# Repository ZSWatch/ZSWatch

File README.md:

# [zswatch.dev](https://zswatch.dev/)

<div align="center">

<sub>
  ZSWatch v4 CNC:ed Stainless Steel (left), Clear Resin 3D print (right)
</sub>
</div>

> **WatchDK** - The ZSWatch development kit ($99) has the same nRF5340 chip and sensors as the final watch, in a larger form factor for development and debugging. Battery optional, runs off USB-C.
>
> [Order from Elecrow](https://www.elecrow.com/zswatch-development-kit.html)
>
> [Quick Start](https://zswatch.dev/docs/getting-started/watchdk-quickstart)

## About

Smartwatch built from scratch, both hardware and software. Built on the [Zephyr™ Project](https://www.zephyrproject.org/) RTOS, hence the name **ZSWatch** (*Zephyr Smartwatch*).

<kbd></kbd>

<sub>ZSWatch Development Kit (WatchDK)</sub>

https://github.com/ZSWatch/ZSWatch/assets/4318648/ec1a94fd-a682-4559-9e68-f3e5bfcbe682

## Documentation

Full documentation is available at **[zswatch.dev](https://zswatch.dev)**:

- [Getting Started](https://zswatch.dev/docs/getting-started/watchdk-quickstart) - WatchDK quick start guide
- [Toolchain & Compiling](https://zswatch.dev/docs/development/toolchain) - Environment setup, building, and flashing
- [Writing Apps](https://zswatch.dev/docs/development/writing_apps) - How to create applications for ZSWatch
- [Hardware Design](https://zswatch.dev/docs/hardware-design) - PCB design documentation

## Features

### Hardware

- nRF5340 BLE chip ([u-blox NORA-B10 module](https://www.u-blox.com/en/product/nora-b1-series-open-cpu))
  - 128 MHz Dual core
  - 512 KB RAM
  - 1 MB Flash
  - 30 MHz SPI for display
- [240x240 round display](https://www.buydisplay.com/catalog/product/view/id/1849/s/240x240-round-ips-tft-lcd-display-1-28-capacitive-touch-circle-screen/) with touch screen
- IMU [Bosch BMI270](https://www.bosch-sensortec.com/media/boschsensortec/downloads/datasheets/bst-bmi270-ds000.pdf) for gesture navigation, wrist-wake, step counting
- Bosch [BMP581](https://www.bosch-sensortec.com/products/environmental-sensors/pressure-sensors/bmp581/) High-performance pressure sensor (~20 cm accuracy)
- ST [LIS2MDLTR](https://www.st.com/resource/en/datasheet/lis2mdl.pdf) Magnetometer
- Macronix [MX25U51245GZ4I00](https://www.mouser.de/datasheet/2/819/MX25U51245G_2c_1_8V_2c_512Mb_2c_v1_4-3371129.pdf) 64 MB external flash
- Broadcom [APDS-9306-065](https://docs.broadcom.com/docs/AV02-4755EN) Light Sensor for automatic brightness control
- Micro Crystal [RV-8263-C8](https://www.microcrystal.com/en/products/real-time-clock-rtc-modules/rv-8263-c8) RTC for time keeping and alarm functions
- Knowles [SPK0641HT4H-1](https://www.knowles.com/docs/default-source/model-downloads/spk0641ht4h-1-rev-a.pdf) I2S microphone for audio recording
- Nordic [nPM1300](https://docs.nordicsemi.com/category/npm1300-category) PMIC for power and system management
- Speaker (Requires HR Extension Board)

#### PCB

All hardware is designed in KiCad. Hardware repos:

- [Watch PCB](https://github.com/ZSWatch/Watch-HW) - 38 mm diameter watch PCB
- [Watch DevKit PCB](https://github.com/ZSWatch/Watch-DevKit-HW) - Larger development board with breakout headers and debug header
- [Extension PCB](https://github.com/ZSWatch/Extension-HW) - Health and audio addon PCB
- [Dock/Breakout PCB](https://github.com/ZSWatch/Dock-HW) - USB-C breakout for debugger and UART access

<kbd></kbd>
#### HR Extension Board (WIP)

The Extension PCB is a small add-on board (approximately 16.8 mm diameter) that plugs into the WatchDK headers. It is still in development and the design, BOM, and firmware support may change.

More background and progress updates:
- https://zswatch.dev/blog/dk-and-hr-integration
- https://zswatch.dev/blog/progress-hw-xip-usb-power
- https://zswatch.dev/blog/progress-hr-fota

Key BOM highlights:
- Analog Devices / Maxim `MAX86141` optical AFE + ams OSRAM `SFH 7016` (RGB/IR LED module) + Vishay `VEMD8082` photodiodes
- Analog Devices / Maxim `MAX32664` biometric sensor hub
- Renesas / Dialog `DA7212` audio codec (speaker support)
- Amphenol `101P014FB110` board-to-board connectors

### Software

- Bluetooth LE communications via the [ZSWatch Companion App](https://zswatch.dev/docs/getting-started/companion_app) (iOS/Android) or [GadgetBridge](https://codeberg.org/Freeyourgadget/Gadgetbridge) (Android)
- Multiple watchfaces (dynamically switchable), showing time, date, battery, weather, steps, notifications, environmental data, and more
- Pop-up notifications
- Application picker with extensible app framework
  - [Settings](app/src/applications/settings/), [Music control](app/src/applications/music_control/), [Compass](app/src/applications/compass/), and many more
- Step counting, gestures, and much more

The watch also supports ESP32 watchfaces from [Felix Biego](https://github.com/fbiego). See [this fork](https://github.com/Kampi/esp32-lvgl-watchface) for details.

### Smartphone Communication

**iOS (recommended):** Use the official [ZSWatch Companion App](https://apps.apple.com/us/app/zswatch/id6759058602) on the App Store. ZSWatch also supports native [Apple Notification Center Service](https://developer.apple.com/library/archive/documentation/CoreBluetooth/Reference/AppleNotificationCenterServiceSpecification/Specification/Specification.html) and [Apple Media Service](https://developer.apple.com/library/archive/documentation/CoreBluetooth/Reference/AppleMediaService_Reference/Specification/Specification.html).

**Android (experimental companion app):** The ZSWatch Companion App currently requires invite access. Request access via [Discord](https://discord.gg/8XfNBmDfbY) or email [mail@zswatch.dev](mailto:mail@zswatch.dev). For a stable experience, use [GadgetBridge](https://codeberg.org/Freeyourgadget/Gadgetbridge).

See [phone setup on zswatch.dev](https://zswatch.dev/docs/getting-started/phone_setup) for details.

### Enclosure/Casing

3D-printed casing with 3D-printed buttons, with an option for CNC:ed metal casing.

## Getting a WatchDK or Building Your Own

**For development:** The [WatchDK](https://zswatch.dev/docs/getting-started/watchdk-quickstart) ($99) is the recommended starting point. It has the same nRF5340 SoC, sensors, and display as the final watch, with breakout headers, USB-C with SWD/UART, power measurement headers, and a debug header. Everything except battery is included. Battery is optional.

Order WatchDK from Elecrow: [www.elecrow.com/zswatch-development-kit.html](https://www.elecrow.com/zswatch-development-kit.html)

**For DIY builders:** Head over to the hardware repos for the for ordering information. The final miniature watch hardware is still being developed.

## Demos

- [HTTP requests over BLE through Gadgetbridge](https://github.com/ZSWatch/ZSWatch/assets/4318648/12d6e754-ceb3-4efd-9a75-d207aaeb0e82)
- [Watchfaces](https://github.com/ZSWatch/ZSWatch/assets/4318648/13e43401-1c00-40ab-866f-e6518e61940d)

## Developing

See the [Toolchain & Build Guide](https://zswatch.dev/docs/development/toolchain) for environment setup, compiling, and flashing.

To learn how to write apps for ZSWatch, see [Writing Apps](https://zswatch.dev/docs/development/writing_apps).

## Licence GPL-3.0

The main difference from MIT is that if anyone wants to build something more with this, they need to also open source their changes back to the project, which I think is fair, so everyone can benefit from those improvements. If you think this is wrong, feel free to contact me and I'm open to change the licence.

## Thanks

### Funding

This project is partly funded through [NGI0 Commons Fund](https://nlnet.nl/commonsfund), a fund established by [NLnet](https://nlnet.nl) with financial support from the European Commission's [Next Generation Internet](https://ngi.eu) program. Learn more at the [NLnet project page](https://nlnet.nl/project/ZSWatch).

### Support

<p align="left">

</p>

**PCBWay** for sponsoring the manufacturing and assembly of prototype PCBs. PCBWay is the recommended manufacturer for PCBs and assembly of ZSWatch.

## Miscellaneous

- [Watch my presentation at Zephyr Developer Summit 2023](https://www.youtube.com/watch?v=MmCzV0jV9hs)

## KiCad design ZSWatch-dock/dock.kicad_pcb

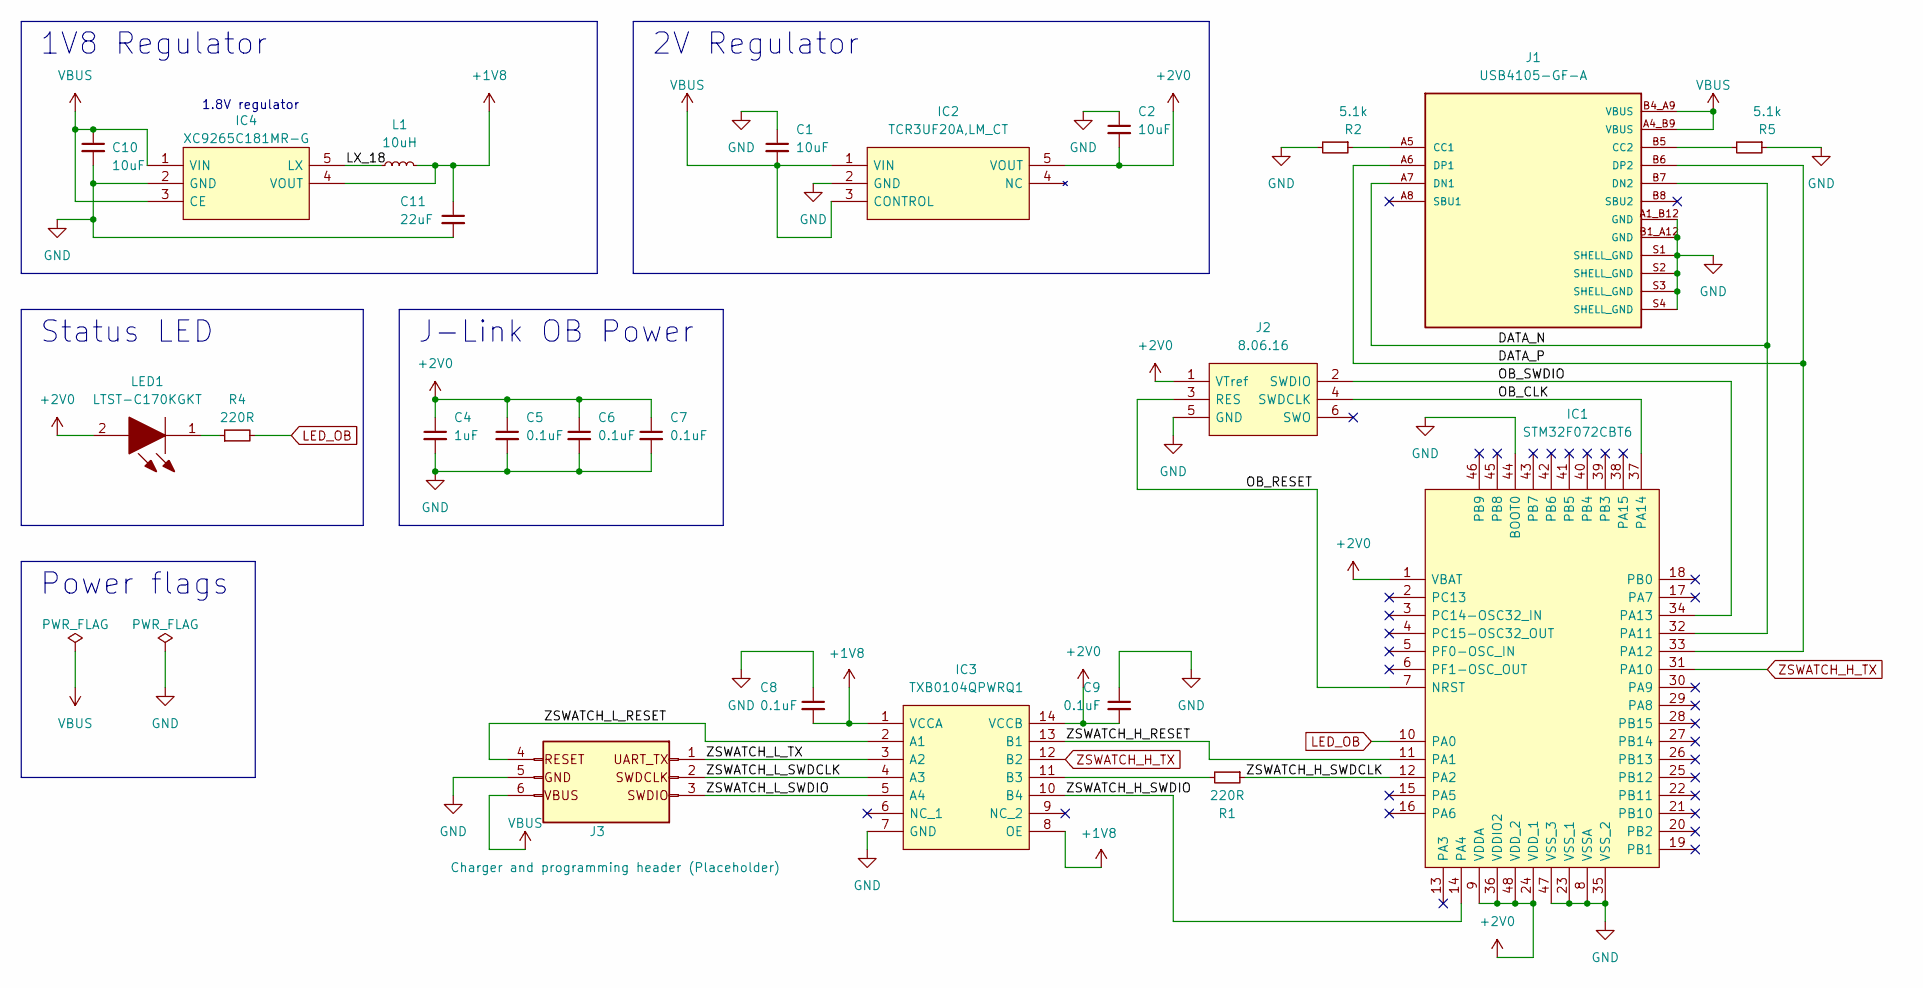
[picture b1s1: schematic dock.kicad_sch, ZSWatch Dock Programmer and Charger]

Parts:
C1, C2, C10: 10uF; C_0603_1608Metric
C4: 1uF; C_0603_1608Metric
C5, C6, C7, C8, C9: 0.1uF; C_0603_1608Metric
C11: 22uF; C_0603_1608Metric
IC1: STM32F072CBT6; QFP50P900X900X160-48N; Mouser Part Number 511-STM32F072CBT6
IC2: TCR3UF20A,LM_CT; TCR3UF20ALMCT; Mouser Part Number 757-TCR3UF20ALMCT
IC3: TXB0104QPWRQ1; SOP65P640X120-14N; Mouser Part Number 595-TXB0104QPWRQ1
IC4: XC9265C181MR-G; SOT95P280X130-5N; Mouser Part Number 865-XC9265C181MR-G
J1: USB4105-GF-A; GCT_USB4105-GF-A; PARTREV A3
J2: 8.06.16; 80616; Mouser Part Number 943-8.06.16
J3: Charger and programming header (Placeholder); rtlecs-6-pin-2-54
L1: 10uH; L_0603_1608Metric
LED1: LTST-C170KGKT; LEDC2012X110N; Mouser Part Number 859-LTST-C170KGKT
R1, R4: 220R; R_0603_1608Metric
R2, R5: 5.1k; R_0603_1608Metric

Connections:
+1V8: C8.2, C11.1, IC3.1 (VCCA), IC3.8 (OE), IC4.4 (VOUT), L1.2
+2V0: C2.2, C4.1, C5.1, C6.1, C7.1, C9.2, IC1.1 (VBAT), IC1.9 (VDDA), IC1.24 (VDD_1), IC1.36 (VDDIO2), IC1.48 (VDD_2), IC2.5 (VOUT), IC3.14 (VCCB), J2.1 (VTref), LED1.2
/DATA_N: IC1.32 (PA11), J1.A7 (DN1), J1.B7 (DN2)
/DATA_P: IC1.33 (PA12), J1.A6 (DP1), J1.B6 (DP2)
/LX_18: IC4.5 (LX), L1.1
/OB_CLK: IC1.37 (PA14), J2.4 (SWDCLK)
/OB_RESET: IC1.7 (NRST), J2.3 (RES)
/OB_SWDIO: IC1.34 (PA13), J2.2 (SWDIO)
/ZSWATCH_H_RESET: IC1.11 (PA1), IC3.13 (B1)
/ZSWATCH_H_SWDCLK: IC1.12 (PA2), R1.1
/ZSWATCH_H_SWDIO: IC1.14 (PA4), IC3.10 (B4)
/ZSWATCH_L_RESET: IC3.2 (A1), J3.4
/ZSWATCH_L_SWDCLK: IC3.4 (A3), J3.2
/ZSWATCH_L_SWDIO: IC3.5 (A4), J3.3
/ZSWATCH_L_TX: IC3.3 (A2), J3.1
GND: C1.1, C2.1, C4.2, C5.2, C6.2, C7.2, C8.1, C9.1, C10.2, C11.2, IC1.8 (VSSA), IC1.23 (VSS_1), IC1.35 (VSS_2), IC1.44 (BOOT0), IC1.47 (VSS_3), IC2.2 (GND), IC3.7 (GND), IC4.2 (GND), J1.A1_B12 (GND), J1.B1_A12 (GND), J1.S1 (SHELL_GND), J1.S2 (SHELL_GND), J1.S3 (SHELL_GND), J1.S4 (SHELL_GND), J2.5 (GND), J3.5, R2.2, R5.1
LED_OB: IC1.10 (PA0), R4.2
unnamed: IC3.11 (B3), R1.2
unnamed: J1.A5 (CC1), R2.1
unnamed: J1.B5 (CC2), R5.2
unnamed: LED1.1, R4.1
VBUS: C1.2, C10.1, IC2.1 (VIN), IC2.3 (CONTROL), IC4.1 (VIN), IC4.3 (CE), J1.A4_B9 (VBUS), J1.B4_A9 (VBUS), J3.6
ZSWATCH_H_TX: IC1.31 (PA10), IC3.12 (B2)

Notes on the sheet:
Status LED
1.8V regulator
1V8 Regulator
Power flags
J-Link OB Power
2V Regulator

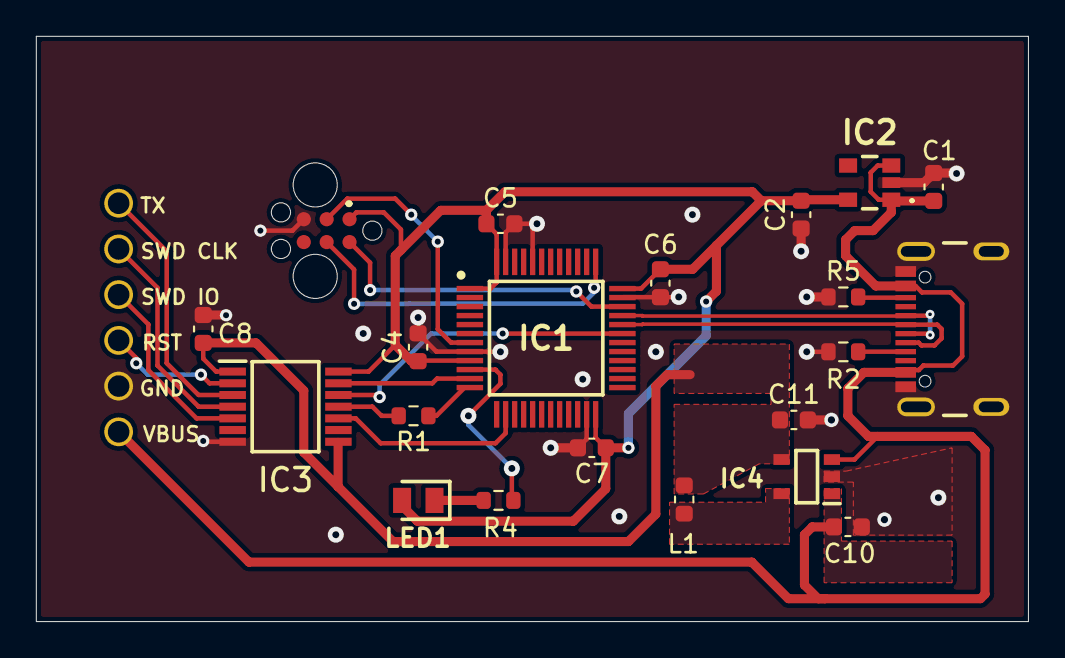
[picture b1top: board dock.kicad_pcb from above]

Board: 2 copper layers, 55.1 x 32.5 mm, 22 parts (0 on the bottom side), 23 nets.

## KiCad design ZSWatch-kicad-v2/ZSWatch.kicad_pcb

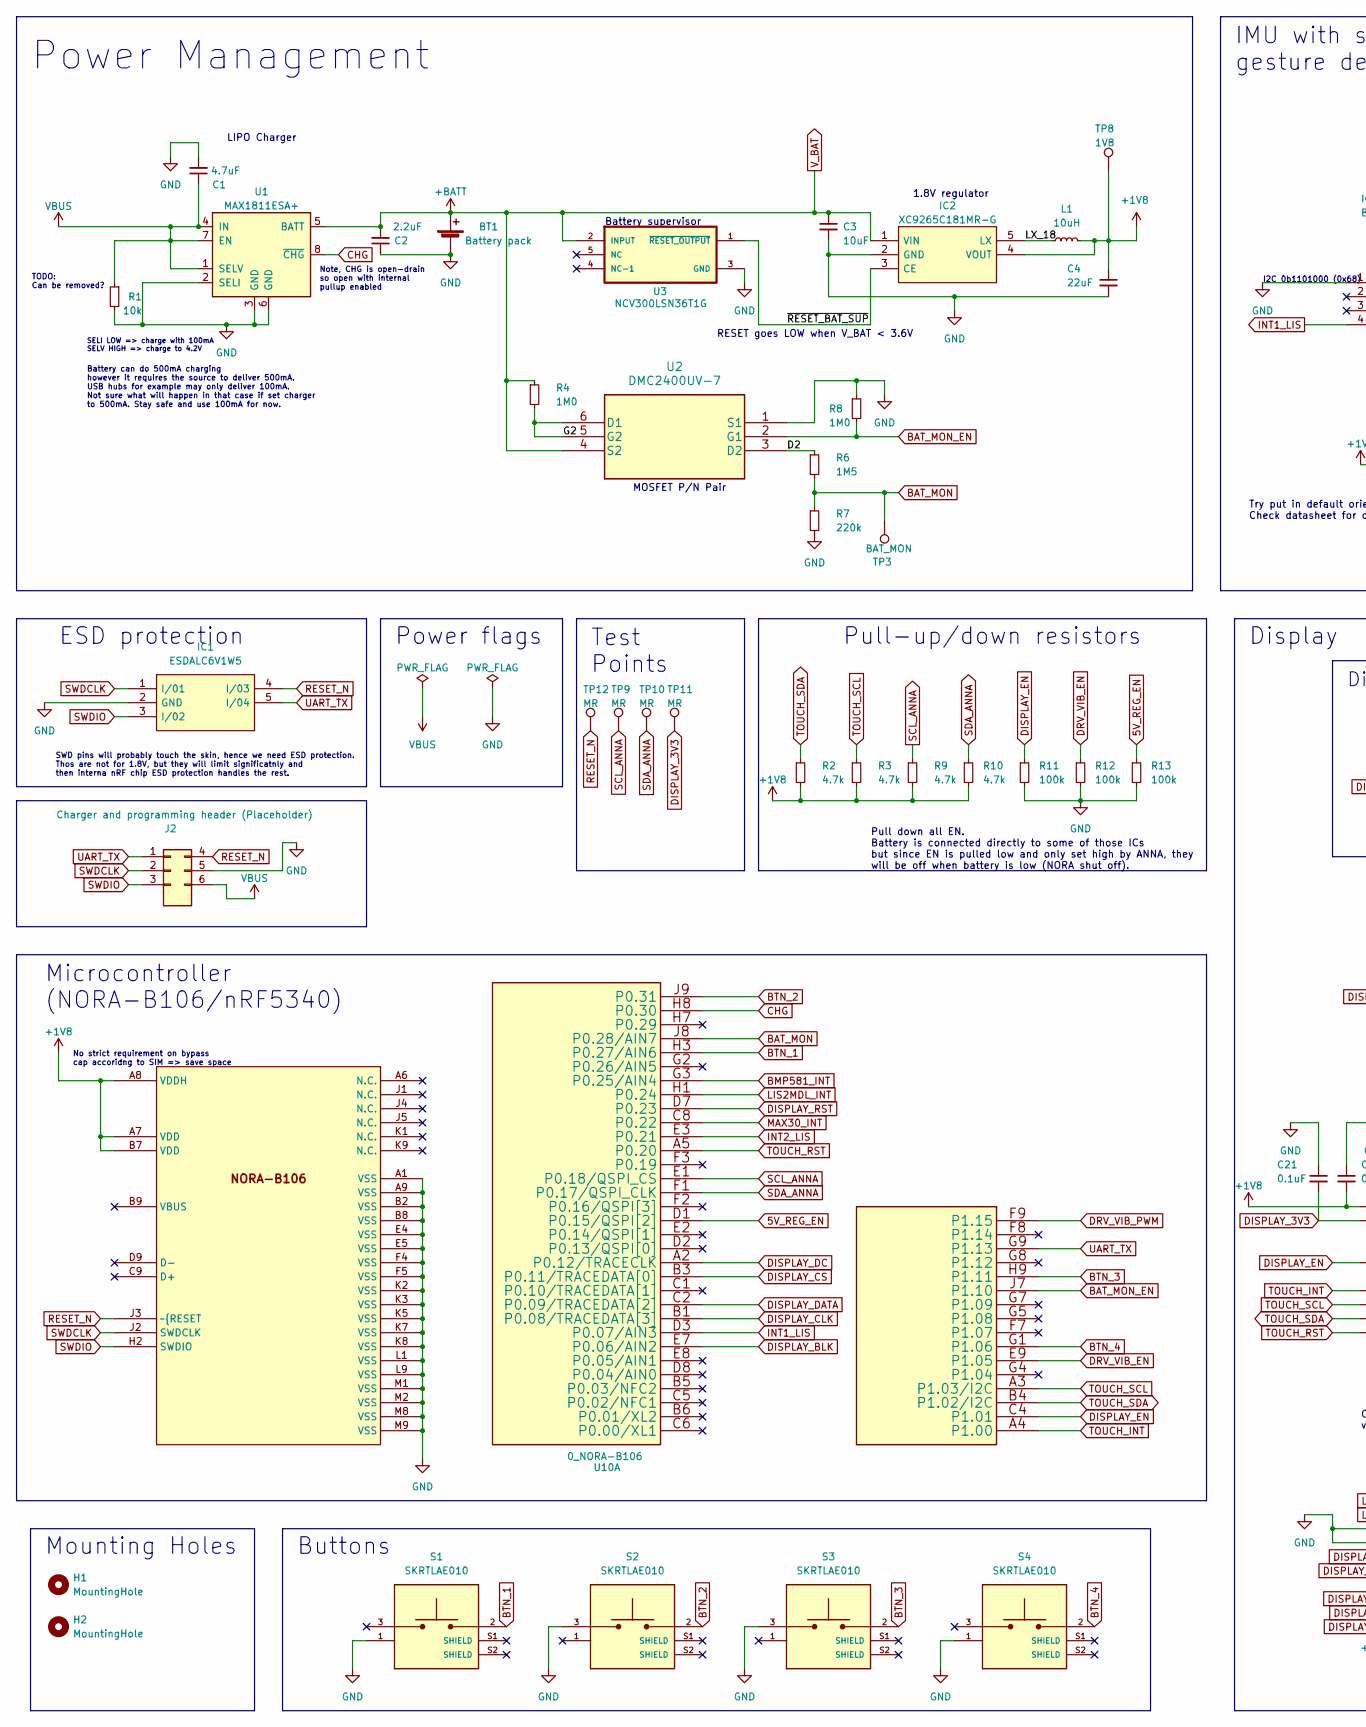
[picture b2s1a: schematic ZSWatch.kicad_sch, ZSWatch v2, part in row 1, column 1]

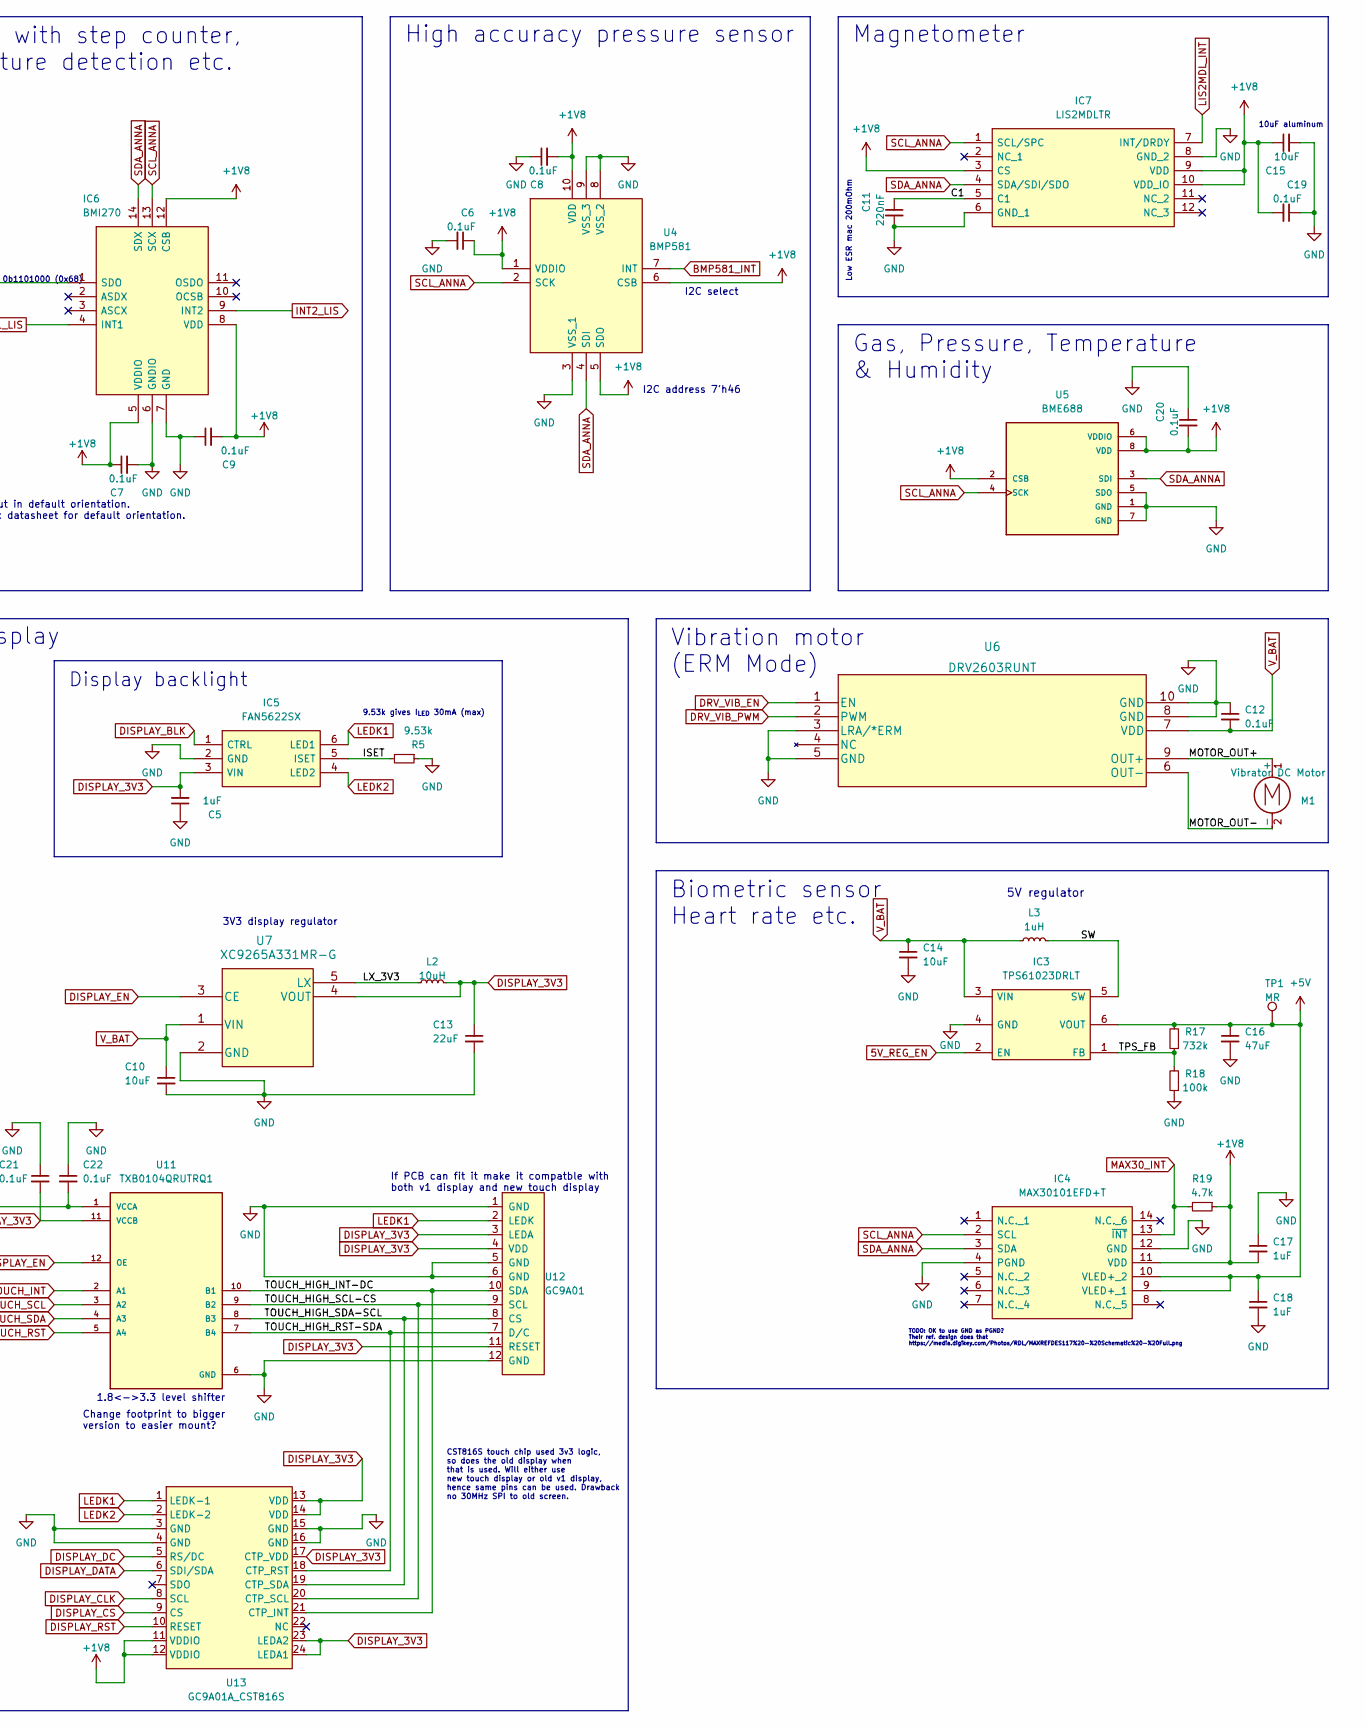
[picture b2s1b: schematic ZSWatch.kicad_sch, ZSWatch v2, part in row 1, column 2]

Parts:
BT1: Battery pack; SolderWire-0.1sqmm_1x02_P3.6mm_D0.4mm_OD1mm
C1: 4.7uF; C_0603_1608Metric
C2: 2.2uF; C_0603_1608Metric
C3, C10, C14, C15: 10uF; C_0603_1608Metric
C4, C13: 22uF; C_0603_1608Metric
C5, C17, C18: 1uF; C_0603_1608Metric
C6, C7, C8, C9, C12, C19, C20, C21, C22: 0.1uF; C_0603_1608Metric
C11: 220nF; C_0603_1608Metric
C16: 47uF; C_0603_1608Metric
H1: MountingHole; MountingHole_3.5mm_Pad_Via
H2: MountingHole; MountingHole_2.2mm_M2
IC1: ESDALC6V1W5; SOT65P210X110-5L; Mouser Part Number 511-ESDALC6V1W5
IC2: XC9265C181MR-G; SOT95P280X130-5N; Mouser Part Number 865-XC9265C181MR-G
IC3: TPS61023DRLT; SOTFL50P160X60-6N; Mouser Part Number 595-TPS61023DRLT
IC4: MAX30101EFD+T; 14-LEAD-OESIP; Mouser Part Number 700-MAX30101EFD+T
IC5: FAN5622SX; SOT95P280X110-6N; Mouser Part Number 512-FAN5622SX
IC6: BMI270; QFN50P300X250X87-14N; Mouser Part Number 262-BMI270
IC7: LIS2MDLTR; LGA-12; Mouser Part Number 511-LIS2MDLTR
J2: Charger and programming header (Placeholder); rtlecs-6-pin-2-54
L1, L2: 10uH; L_0603_1608Metric
L3: 1uH; L_0603_1608Metric
M1: Vibrator DC Motor; TestPoint_2Pads_Pitch2.54mm_Drill0.8mm
R1: 10k; R_0603_1608Metric
R2, R3, R9, R10, R19: 4.7k; R_0603_1608Metric
R4, R8: 1M0; R_0603_1608Metric
R5: 9.53k; R_0603_1608Metric
R6: 1M5; R_0603_1608Metric
R7: 220k; R_0603_1608Metric
R11, R12, R13, R18: 100k; R_0603_1608Metric
R17: 732k; R_0603_1608Metric
S1, S2, S3, S4: SKRTLAE010; SW_SKRTLAE010; PARTREV --
TP1, TP9, TP10, TP11, TP12: MR; TestPoint_Pad_D1.0mm
TP3: BAT_MON; TestPoint_Pad_D1.0mm
TP8: 1V8; TestPoint_Pad_D1.0mm
U1: MAX1811ESA+; SOIC127P600X175-8N
U2: DMC2400UV-7
U3: NCV300LSN36T1G; SOT95P275X110-5N
U4: BMP581; Mouser Part Number 262-BMP581
U5: BME688; IC_BME688; PARTREV 1.0
U6: DRV2603RUNT
U7: XC9265A331MR-G; SOT95P280X130-5N
U10: 0_NORA-B106; NORA_LGA82R_1430X1040X180_ANT; MANUFACTURER P/N NORA-B106-00B
U11: TXB0104QRUTRQ1; HPA01164RUTR; PARTREV 4210580/C 06/12
U12: GC9A01; GC9A01_disp_smaller
U13: GC9A01A_CST816S; ER-24F24-04

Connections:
5V_REG_EN: IC3.2 (EN), R13.1, U10.D1 (P0.15/QSPI[2])
+1V8: C4.1, C6.1, C7.1, C8.2, C9.2, C15.1, C17.2, C19.2, C20.2, C22.2, IC2.4 (VOUT), IC4.11 (VDD), IC6.5 (VDDIO), IC6.8 (VDD), IC6.12 (CSB), IC7.3 (CS), IC7.9 (VDD), IC7.10 (VDD_IO), L1.2, R2.2, R3.2, R9.2, R10.2, R19.1, TP8.1, U4.1 (VDDIO), U4.5 (SDO), U4.6 (CSB), U4.10 (VDD), U5.2 (CSB), U5.6 (VDDIO), U5.8 (VDD), U10.A7 (VDD), U10.A8 (VDDH), U10.B7 (VDD), U11.1 (VCCA), U13.11 (VDDIO), U13.12 (VDDIO)
+5V: C16.1, C18.1, IC3.6 (VOUT), IC4.9 (VLED+_1), IC4.10 (VLED+_2), R17.2, TP1.1
/C1: C11.1, IC7.5 (C1)
/D2: R6.1, U2.3 (D2)
/G2: R4.2, U2.5 (G2), U2.6 (D1)
/ISET: IC5.5 (ISET), R5.2
/LX_3V3: L2.1, U7.5 (LX)
/LX_18: IC2.5 (LX), L1.1
/MOTOR_OUT+: M1.1 (+), U6.9 (OUT+)
/MOTOR_OUT-: M1.2 (-), U6.6 (OUT-)
/SW: IC3.5 (SW), L3.2
/TOUCH_HIGH_INT-DC: U11.10 (B1), U12.10 (SDA), U13.21 (CTP_INT)
/TOUCH_HIGH_RST-SDA: U11.7 (B4), U12.7 (D/C), U13.18 (CTP_RST)
/TOUCH_HIGH_SCL-CS: U11.9 (B2), U12.9 (SCL), U13.20 (CTP_SCL)
/TOUCH_HIGH_SDA-SCL: U11.8 (B3), U12.8 (CS), U13.19 (CTP_SDA)
/TPS_FB: IC3.1 (FB), R17.1, R18.2
/~RESET_BAT_SUP: IC2.3 (CE), U3.1 (~RESET_OUTPUT)
BAT_MON: R6.2, R7.1, TP3.1, U10.J8 (P0.28/AIN7)
BAT_MON_EN: R8.2, U2.2 (G1), U10.J7 (P1.10)
BMP581_INT: U4.7 (INT), U10.G3 (P0.25/AIN4)
BTN_1: S1.2, U10.H3 (P0.27/AIN6)
BTN_2: S2.2, U10.J9 (P0.31)
BTN_3: S3.2, U10.H9 (P1.11)
BTN_4: S4.2, U10.G1 (P1.06)
CHG: U1.8 (~CHG), U10.H8 (P0.30)
DISPLAY_3V3: C5.2, C13.1, C21.2, IC5.3 (VIN), L2.2, TP11.1, U7.4 (VOUT), U11.11 (VCCB), U12.3 (LEDA), U12.4 (VDD), U12.11 (RESET), U13.13 (VDD), U13.14 (VDD), U13.17 (CTP_VDD), U13.23 (LEDA2), U13.24 (LEDA1)
DISPLAY_BLK: IC5.1 (CTRL), U10.E7 (P0.06/AIN2)
DISPLAY_CLK: U10.B1 (P0.08/TRACEDATA[3]), U13.8 (SCL)
DISPLAY_CS: U10.B3 (P0.11/TRACEDATA[0]), U13.9 (CS)
DISPLAY_DATA: U10.C2 (P0.09/TRACEDATA[2]), U13.6 (SDI/SDA)
DISPLAY_DC: U10.A2 (P0.12/TRACECLK), U13.5 (RS/DC)
DISPLAY_EN: R11.1, U7.3 (CE), U10.C4 (P1.01), U11.12 (OE)
DISPLAY_RST: U10.D7 (P0.23), U13.10 (RESET)
DRV_VIB_EN: R12.1, U6.1 (EN), U10.E9 (P1.05)
DRV_VIB_PWM: U6.2 (PWM), U10.F9 (P1.15)
GND: BT1.2 (-), C1.2, C2.1, C3.2, C4.2, C5.1, C6.2, C7.2, C8.1, C9.1, C10.2, C11.2, C12.1, C13.2, C14.2, C15.2, C16.2, C17.1, C18.2, C19.1, C20.1, C21.1, C22.1, IC1.2 (GND), IC2.2 (GND), IC3.4 (GND), IC4.4 (PGND), IC4.12 (GND), IC5.2 (GND), IC6.1 (SDO), IC6.6 (GNDIO), IC6.7 (GND), IC7.6 (GND_1), IC7.8 (GND_2), J2.5, R1.2, R5.1, R7.2, R8.1, R11.2, R12.2, R13.2, R18.1, S1.1, S2.3, S3.3, S4.1, U1.2 (SELI), U1.3 (GND), U1.6 (GND), U2.1 (S1), U3.3 (GND), U4.3 (VSS_1), U4.8 (VSS_2), U4.9 (VSS_3), U5.1 (GND), U5.5 (SDO), U5.7 (GND), U6.3 (LRA/*ERM), U6.5 (GND), U6.8 (GND), U6.10 (GND), U7.2 (GND), U10.A1 (VSS), U10.A9 (VSS), U10.B2 (VSS), U10.B8 (VSS), U10.E4 (VSS), U10.E5 (VSS), U10.F4 (VSS), U10.F5 (VSS), U10.K2 (VSS), U10.K3 (VSS), U10.K5 (VSS), U10.K7 (VSS), U10.K8 (VSS), U10.L1 (VSS), U10.L9 (VSS), U10.M1 (VSS), U10.M2 (VSS), U10.M8 (VSS), U10.M9 (VSS), U11.6 (GND), U12.1 (GND), U12.5 (GND), U12.6 (GND), U12.12 (GND), U13.3 (GND), U13.4 (GND), U13.15 (GND), U13.16 (GND)
INT1_LIS: IC6.4 (INT1), U10.D3 (P0.07/AIN3)
INT2_LIS: IC6.9 (INT2), U10.E3 (P0.21)
LEDK1: IC5.6 (LED1), U12.2 (LEDK), U13.1 (LEDK-1)
LEDK2: IC5.4 (LED2), U13.2 (LEDK-2)
LIS2MDL_INT: IC7.7 (INT/DRDY), U10.H1 (P0.24)
MAX30_INT: IC4.13 (~INT), R19.2, U10.C8 (P0.22)
RESET_N: IC1.4 (I/03), J2.4, TP12.1, U10.J3 (~{RESET)
SCL_ANNA: IC4.2 (SCL), IC6.13 (SCX), IC7.1 (SCL/SPC), R9.1, TP9.1, U4.2 (SCK), U5.4 (SCK), U10.E1 (P0.18/QSPI_CS)
SDA_ANNA: IC4.3 (SDA), IC6.14 (SDX), IC7.4 (SDA/SDI/SDO), R10.1, TP10.1, U4.4 (SDI), U5.3 (SDI), U10.F1 (P0.17/QSPI_CLK)
SWDCLK: IC1.1 (I/01), J2.2, U10.J2 (SWDCLK)
SWDIO: IC1.3 (I/02), J2.3, U10.H2 (SWDIO)
TOUCH_INT: U10.A4 (P1.00), U11.2 (A1)
TOUCH_RST: U10.A5 (P0.20), U11.5 (A4)
TOUCH_SCL: R3.1, U10.A3 (P1.03/I2C), U11.3 (A2)
TOUCH_SDA: R2.1, U10.B4 (P1.02/I2C), U11.4 (A3)
UART_TX: IC1.5 (I/04), J2.1, U10.G9 (P1.13)
VBUS: C1.1, J2.6, R1.1, U1.1 (SELV), U1.4 (IN), U1.7 (EN)
V_BAT: BT1.1 (+), C2.2, C3.1, C10.1, C12.2, C14.1, IC2.1 (VIN), IC3.3 (VIN), L3.1, R4.1, U1.5 (BATT), U2.4 (S2), U3.2 (INPUT), U6.7 (VDD), U7.1 (VIN)

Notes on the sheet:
Test Points
Display backlight
Battery can do 500mA charging however it requires the source to deliver 500mA. USB hubs for example may only deliver 100mA. Not sure what will happen in that case if set charger to 500mA. Stay safe and use 100mA for now.
1.8<->3.3 level shifter
I2C select
Biometric sensor Heart rate etc.
Gas, Pressure, Temperature & Humidity
High accuracy pressure sensor
3V3 display regulator
Pull-up/down resistors
MOSFET P/N Pair
Power Management
SELI LOW => charge with 100mA SELV HIGH => charge to 4.2V
Battery supervisor
RESET goes LOW when V_BAT < 3.6V
I2C address 7'h46
Low ESR mac 200mOhm
_{I2C 0b1101000 (0x68)}
Change footprint to bigger version to easier mount?
TODO: Can be removed?
Buttons
Microcontroller (NORA-B106/nRF5340)
TODO: OK to use GND as PGND? Their ref. design does that https://media.digikey.com/Photos/RDL/MAXREFDES117%20-%20Schematic%20-%20Full.png
Note, CHG is open-drain so open with internal pullup enabled
No strict requirement on bypass cap accoridng to SIM => save space
Power flags
9.53k gives I_{LED} 30mA (max)
Magnetometer
SWD pins will probably touch the skin, hence we need ESD protection. Thos are not for 1.8V, but they will limit significatnly and then interna nRF chip ESD protection handles the rest.
Pull down all EN. Battery is connected directly to some of those ICs but since EN is pulled low and only set high by ANNA, they will be off when battery is low (NORA shut off).
Try put in default orientation. Check datasheet for default orientation.
IMU with step counter, gesture detection etc.
LIPO Charger
5V regulator
If PCB can fit it make it compatble with both v1 display and new touch display
ESD protection
Vibration motor (ERM Mode)
Mounting Holes
CST816S touch chip used 3v3 logic, so does the old display when that is used. Will either use new touch display or old v1 display, hence same pins can be used. Drawback no 30MHz SPI to old screen.
Display

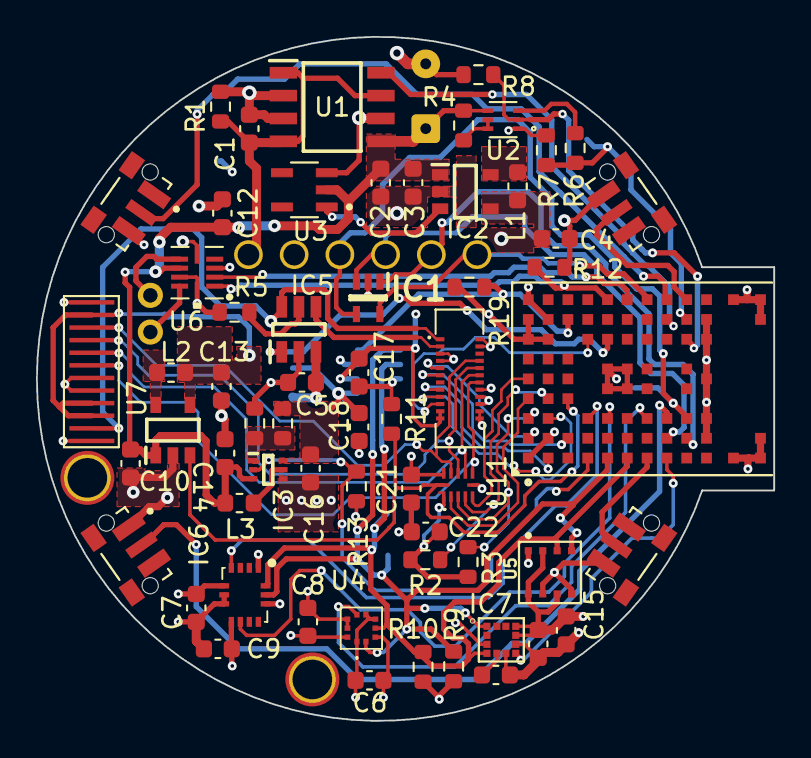
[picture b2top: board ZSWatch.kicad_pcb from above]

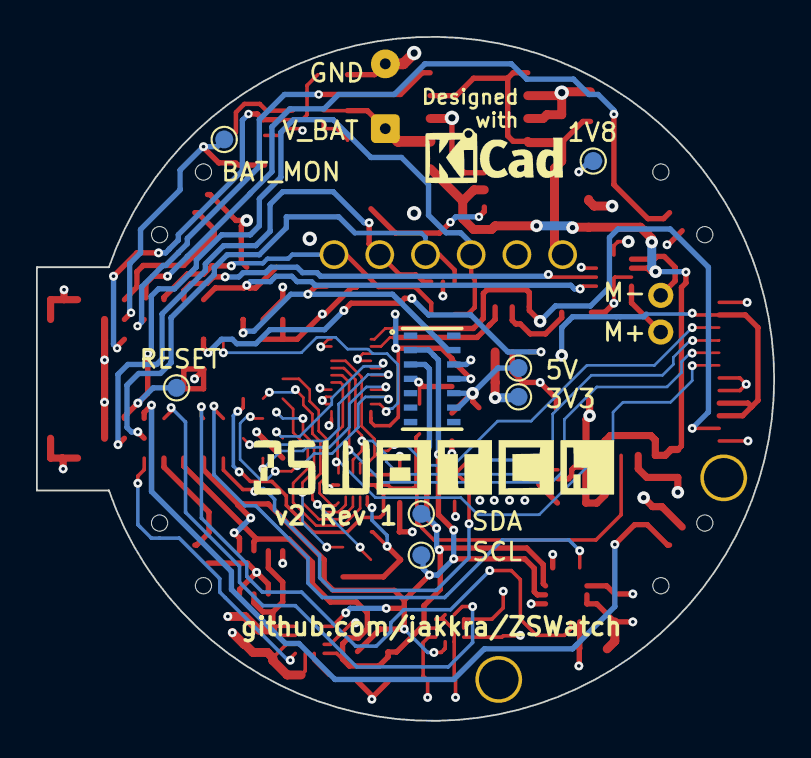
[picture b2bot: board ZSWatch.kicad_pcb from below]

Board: 4 copper layers, 41.0 x 38.0 mm, 74 parts (9 on the bottom side), 55 nets.

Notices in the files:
README.md:
License: GPL 3.0
parts and their libraries:
Copyright 2021 Accelerated Designs. All rights reserved.
